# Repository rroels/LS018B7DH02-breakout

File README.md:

# Sharp LS018B7DH02 Memory LCD breakout board

> [!WARNING]
> The information and material (code, designs, files, ...) are provided "AS IS". We make no representation or warranty of any kind, express or implied, regarding the accuracy, adequacy, validity, reliability, availability, or completeness of any information or material. Use this at your own risk.

## Introduction

This repository contains a small breakout board for the Sharp LS018B7DH02 Memory LCD.

Also see this repository for an Arduino driver for this display:
[https://github.com/rroels/Sharp\_LS018B7DH02\_Arduino](https://github.com/rroels/Sharp_LS018B7DH02_Arduino)

## Design Considerations

### "Refresh" signal

To explain in layman's terms, this type of display needs a periodic "refresh signal" (even if you don't intend to change the displayed image), otherwise pixels start to get stuck (until the display is reset). 

It's not actually a refresh of the display, but rather a "polarity inversion".  A shortended explanation from the Sharp "[Programming Sharp’s Memory LCDs](https://www.sharpsde.com/fileadmin/products/Displays/2016_SDE_App_Note_for_Memory_LCD_programming_V1.3.pdf)" documentation:
 
> When designing with a memory LCD panel, a decision must be made as to how VCOM will be generated. VCOM is an alternating signal that prevents a DC bias from being built up within the panel. If this DC bias is
allowed to accumulate, it will eventually reach the point where the state of the liquid crystals in the panel
cells cannot be changed by the panel electronics and the cells will no longer change state. 

> It must be supplied using one of two methods: software, or external clock. The mode is selected by the EXTMODE pin on the interface.

> * If external clock is selected [EXTMODE = H], the clock should be supplied on the EXTCOMM pin. 
> * When the software clock is selected [EXTMODE = L], bit V of the command bit string sets the state of VCOM.

Depending on the chosen method, hardware is configured in one of two ways:

This breakout board should allow either hardware setup. This is done by setting a jumper that connects EXTMODE to either VSS or VDD. The user is still responsible for providing the refresh signal, either via software commands or via an external clock signal, depending on how the jumper is placed. 

When the user chooses for the software clock option, EXTCOMIN should be tied to GND. This is also possible with a jumper.

### VDD = VDDA

Typically, most designs combine digital power supply and analog power supply. This leaves the option to supply them seperately, but they can also be combined by placing a jumper. When the jumper is in placed, you only need to connect either VDD or VDDA.

### SCS Pull-down

It's good practise to have a pull-up for SPI chip-select lines:
* https://dorkbotpdx.org/blog/paul/better_spi_bus_design_in_3_steps/
* https://hackaday.com/2014/11/25/better-spi-bus-design/

HOWEVER, note that the SCS is active high for this display, and not active low like most SPI devices. For this reason, we provide an optional pull-down resistor, instead of a pull-up resistor. This can be enabled by placing a jumper.

## Schematics

We base ourselves on the following recommended circuits from the datasheet:

Which led to the following schematics:

## Bill of Materials (BOM)

|Reference|Footprint|Value|Qty|
|---|---|---|---|
|J6,J4,J5|PinHeader\_1x02\_P2.54mm\_Vertical|Conn\_01x02|3|
|C1|C_0603\_1608Metric\_Pad1.08x0.95mm\_HandSolder|0.1uF|1|
|C3,C2|C\_0603\_1608Metric\_Pad1.08x0.95mm\_HandSolder|1uF|2|
|J3|PinHeader\_1x03\_P2.54mm\_Vertical|Conn\_01x03|1|
|J2|5034801000|Conn\_01x10|1|
|J1|PinHeader\_1x09_P2.54mm\_Horizontal|Conn\_01x09|1|
|R1|R\_0603\_1608Metric\_Pad0.98x0.95mm\_HandSolder|10K|1|

See image of the PCB below to have a better idea of what these components look like. 

All capacitors and resistors and SMD 0603. Instead of the horizontal pin header I used, a vertical pin header will also work fine (as long as the pitch is 2.54mm).

## How to Obtain the Physical PCB

The Gerber file is in this repository (`gerber/LS018B7DH02-breakout.zip`). Simply upload this file a PCB manufacturer of your choice (JLPCB, PCBWay, ...), and you they will make it for you for as low as \$5 for 5 pieces (with the cheapest shipping option, which can take a few weeks).

> [!WARNING]
> Note that you will still have to solder the components onto the PCB yourself!

## How to Edit Design

Everything you need to edit this design in KiCad 8 is included in the repository. 

However, this project uses symbols, footprints and 3D models from [Component Search Engine](https://componentsearchengine.com/). Their license allows us to do pretty much whatever we want with them, except redistributing them. For this reason I can't include them in this repository. 

If you would like to edit the design yourself, you will need to download the following component libraries from [https://componentsearchengine.com/](https://componentsearchengine.com/) (it's free!):

* [https://componentsearchengine.com/part-view/503480-1000/Molex](https://componentsearchengine.com/part-view/503480-1000/Molex) 

From the downloaded zip file, move the content of the `KiCad` and `3D` subfolders into the project structure, so that the end-result looks like this:

The KiCad project is configured to look for these files in these locations, using relative paths, so no changes to the project itself are required. 

## Related Sources

* [https://www.sharpsde.com/products/displays/model/ls018b7dh02/](https://www.sharpsde.com/products/displays/model/ls018b7dh02/)
* [https://www.sharpsde.com/fileadmin/products/Displays/Specs/LS018B7DH02\_31Oct23\_Spec\_LD-2023X08.pdf](https://www.sharpsde.com/fileadmin/products/Displays/Specs/LS018B7DH02_31Oct23_Spec_LD-2023X08.pdf)
* [https://www.sharpsde.com/fileadmin/products/Displays/2016\_SDE\_App\_Note\_for\_Memory\_LCD\_programming\_V1.3.pdf](https://www.sharpsde.com/fileadmin/products/Displays/2016_SDE_App_Note_for_Memory_LCD_programming_V1.3.pdf)
* [https://learn.adafruit.com/adafruit-sharp-memory-display-breakout/downloads#schematic-and-fabrication-print-2-dot-7-display-3070007](https://learn.adafruit.com/adafruit-sharp-memory-display-breakout/downloads#schematic-and-fabrication-print-2-dot-7-display-3070007)
* [https://bridle.tiac-systems.net/doc/3.2.0/zephyr/boards/shields/ls0xx_generic/doc/index.html](https://bridle.tiac-systems.net/doc/3.2.0/zephyr/boards/shields/ls0xx_generic/doc/index.html)
* [https://github.com/lvgl/lv_drivers/blob/master/display/SHARP_MIP.c](https://github.com/lvgl/lv_drivers/blob/master/display/SHARP_MIP.c)
* [https://kuzyatech.com/sharp-memory-lcd-breakout-a2](https://kuzyatech.com/sharp-memory-lcd-breakout-a2)

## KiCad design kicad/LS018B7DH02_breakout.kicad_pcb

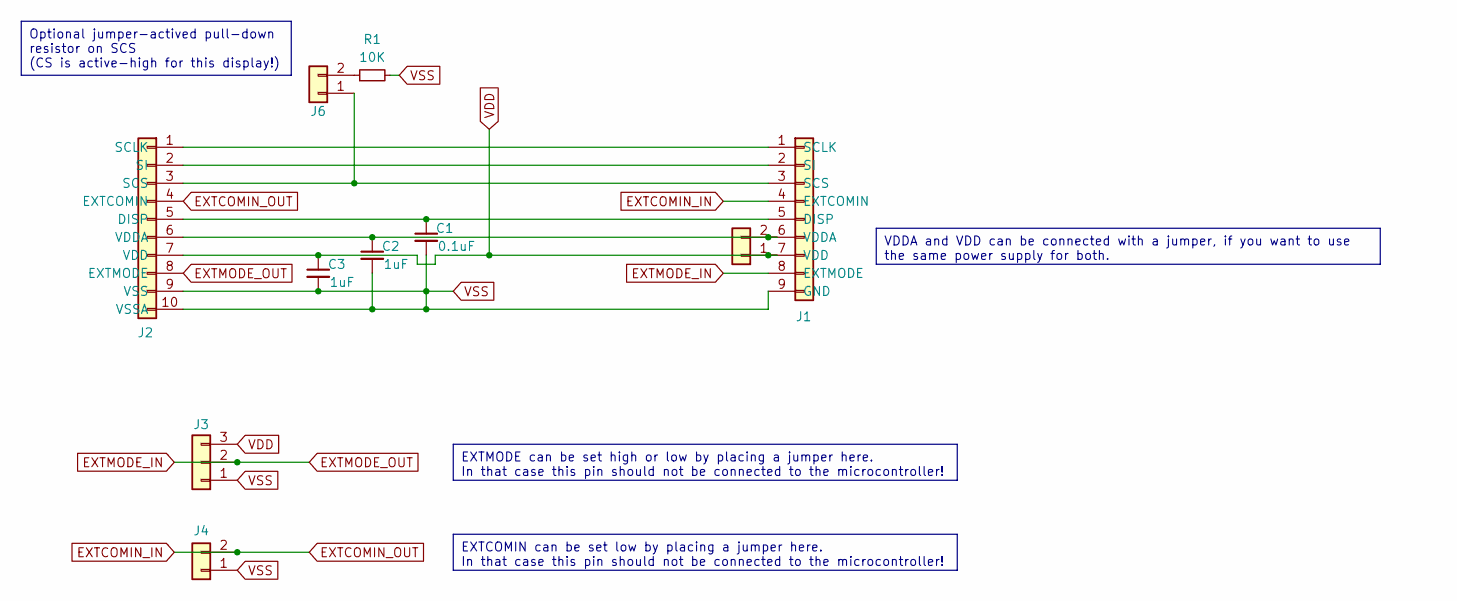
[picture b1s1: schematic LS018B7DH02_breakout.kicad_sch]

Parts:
C1: 0.1uF; C_0603_1608Metric_Pad1.08x0.95mm_HandSolder
C2, C3: 1uF; C_0603_1608Metric_Pad1.08x0.95mm_HandSolder
J1: Conn_01x09; PinHeader_1x09_P2.54mm_Horizontal
J2: Conn_01x10; 5034801000
J3: Conn_01x03; PinHeader_1x03_P2.54mm_Vertical
J4, J5, J6: Conn_01x02; PinHeader_1x02_P2.54mm_Vertical
R1: 10K; R_0603_1608Metric_Pad0.98x0.95mm_HandSolder

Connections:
EXTCOMIN_IN: J1.4 (EXTCOMIN), J2.4 (EXTCOMIN), J4.2
EXTMODE_IN: J1.8 (EXTMODE), J2.8 (EXTMODE), J3.2
unnamed: C1.1, J1.5 (DISP), J2.5 (DISP)
unnamed: J1.1 (SCLK), J2.1 (SCLK)
unnamed: J1.3 (SCS), J2.3 (SCS), J6.1
unnamed: J1.2 (SI), J2.2 (SI)
unnamed: C2.1, J1.6 (VDDA), J2.6 (VDDA), J5.2
unnamed: J6.2, R1.1
VDD: C3.1, J1.7 (VDD), J2.7 (VDD), J3.3, J5.1
VSS: C1.2, C2.2, C3.2, J1.9 (GND), J2.9 (VSS), J2.10 (VSSA), J3.1, J4.1, R1.2

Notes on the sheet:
VDDA and VDD can be connected with a jumper, if you want to use the same power supply for both.
EXTMODE can be set high or low by placing a jumper here. In that case this pin should not be connected to the microcontroller!
Optional jumper-actived pull-down resistor on SCS (CS is active-high for this display!)
EXTCOMIN can be set low by placing a jumper here. In that case this pin should not be connected to the microcontroller!

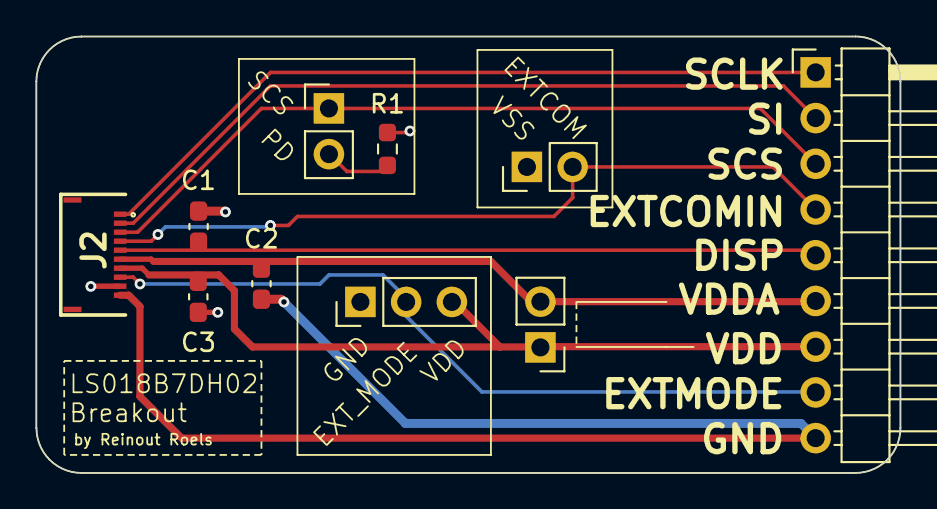
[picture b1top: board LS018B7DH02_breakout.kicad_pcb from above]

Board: 2 copper layers, 48.0 x 24.2 mm, 10 parts (0 on the bottom side), 10 nets.

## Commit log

2024-08-01 add gitignore
2024-08-01 add datasheets
2024-08-01 add gerbers
2024-08-01 add kicad files
